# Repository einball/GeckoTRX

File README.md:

# GeckoTRX
GeckoTRX Assembly Design Files

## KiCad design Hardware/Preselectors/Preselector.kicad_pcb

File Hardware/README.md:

# GeckoTRX Hardware Design Files

GeckoTRX Hardware Repository

## Getting Started

GeckoTRX is a palm-sized Software Defined Radio with a focus on my own education and be a fun project in my spare time. The repository you are looking at is hosting the front assembly of the project, both hardware design files and software source files required to build the project. If you haven't done any programming or software development yet, or just want to download the latest release of the firmware, you may want to have a look at the [Quickstart Guide](#).

## Prerequisites

In order to view the hardware design files, you will need to obtain a copy of [Autodesk's EagleCAD](https://www.autodesk.com/products/eagle/) which is freely available to view the hardware design files. 

The front assembly uses a EFM8BB1 microcontroller which features a 8051 core alongside with the neccessary peripherals to drive the LED's to indicate the transceivers status.

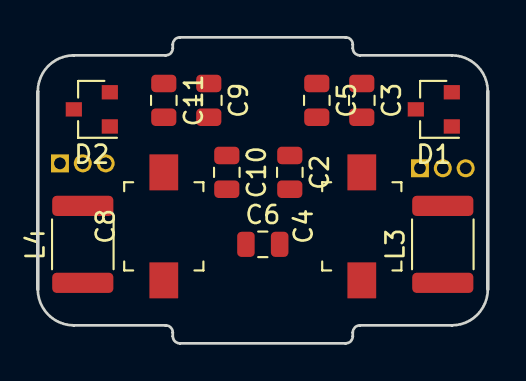
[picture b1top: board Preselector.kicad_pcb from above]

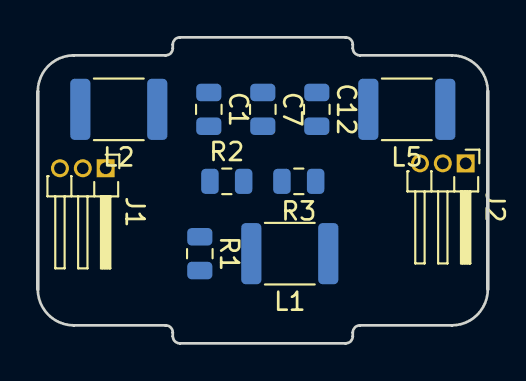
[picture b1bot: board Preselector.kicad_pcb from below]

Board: 2 copper layers, 25.0 x 16.9 mm, 24 parts (11 on the bottom side), 11 nets, no tracks yet.

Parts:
C1, C2, C3, C5, C6, C7, C9, C10, C11, C12: 68p; C_0805_2012Metric
C4, C8: C_Variable; C_Trimmer_Murata_TZB4-B
D1, D2: D; SOT-23
J1, J2: Conn_01x03_Male; PinHeader_1x03_P1.27mm_Horizontal
L1, L2, L5: L_Core_Ferrite; L_1812_4532Metric
L3, L4: L; L_1812_4532Metric
R1, R2, R3: 100R; R_0805_2012Metric

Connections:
/BPF_EN_80M: J1.2, L1.2
/PRE_IN: D2.1, J2.3
/PRE_OUT: D1.1, J1.1
GND: C1.1, C3.1, C5.1, C7.1, C9.1, C11.1, C12.1, J1.3, J2.1, J2.2, L3.2, L4.2, R1.2
unnamed: C1.2, L2.2, R2.1
unnamed: C2.1, C3.2, C4.2, C5.2, D1.2, L2.1
unnamed: C2.2, C4.1, C6.2, L3.1
unnamed: C7.2, L1.1, R1.1, R2.2, R3.2
unnamed: C8.2, C9.2, C10.1, C11.2, D2.2, L5.1
unnamed: C6.1, C8.1, C10.2, L4.1
unnamed: C12.2, L5.2, R3.1

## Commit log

2018-10-02 Add gitignore
2018-10-02 Fix Library include in Includes
2018-10-02 Remove multiline expression
2018-10-02 Add cmake support
2018-10-02 Add cmake suport
2018-10-02 Add multiple READMEs
2018-10-17 Add stepdown converters
2018-10-27 Add sides, add Tayloe Detector
2018-11-16 Order sides
2018-11-28 Adds SN74CBT3253 to Bottom
2018-12-11 Finish version 0.1 of front
2018-12-11 Advance layout bottom
2018-12-12 Front board cleanup
2018-12-26 Add RF Buffer
2019-01-10 Add various parts
2019-03-18 Add KiCAD Bottom
2019-03-18 Add KiCAd project file
2019-04-25 Update board Projektarbeit
2019-04-25 KiCAD advancements
2019-07-10 PCB v2 0 airwires
2019-07-12 PCB v2 done
2021-02-04 keine ahnung, aber weitergemacht
